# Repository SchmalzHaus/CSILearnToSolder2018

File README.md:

# LearnToSolder2018

## Introduction

In late 2018/early 2019 I taught a learn to solder class at the company I work for (CSI - www.csi360.com) because I thought it would be something enjoyable that I could teach my coworkers. Most of the class attendees had never soldered before. I designed a special circuit board for this class which mimics the functionality of one of the devices the company sells, but in miniature.

This site contains all of the information related to the class. If you want to learn more about how to solder, if you want to know what you need to purchase so you can solder at home, or if you want to make more of these boards for yourself or your organization, this site has everything you'll need.

If you want to reach Brian Schmalz (brian@schmalzaus.com) to ask any questions, please do so. 

All text files and designs on this site are Open Source. You are free to use these files and do whatever you wish with them.

## Design Details

The circuit board is designed in the shape of an OAD (Orbital Atherectomy Device). It has a speed switch, which wakes it up from sleep and allows you to select one of three speeds for the motor. The start/stop switch turns the motor on and off. The three green speed LEDs indicate which speed is currently selected. A small microcontroller has code which reads the switches and controls the LEDs and motor. A small FET is used to PWM the motor so various speeds can be achieved. The 3V lithium battery provides power to the circuit. The microcontroller stays asleep until the speed switch is pressed, and goes back to sleep (turning off the motor and LEDs) after 30 seconds of inactivity.

The code for the PIC microcontroller is included in this git repo, as well as the resulting HEX file. If you want to make this board on your own, you will need to program the microcontrollers with this HEX file. An ISCP connector footprint is provided under the battery holder so that the micro can be programed from the back by pressing in a 1x5 .1" header.

## CSI Learn T oSolder 2018 Kit Contents

* Qty 1 Bare Circuit Board (see above image for back and front views of the bare board) - note that the board used for the class already had the surface mount parts (3 of them) soldered on before the students got the boards.
* Qty 1 Speed Switch
* Qty 1 Start Switch
* Qty 3 Green LEDs
* Qty 1 Battery Holder
* Qty 1 Battery
* Qty 1 vibration motor
* Qty 1 black zip tie
* Qty 4 stick on rubber feet

## Tools

To solder electronic kits together, you will need (at a minimum)

### Soldering Iron

We do not recommend buying a soldering iron unless it is 'temperature controlled'. This means you get to set the tip temperature with a knob or buttons, and the iron will only heat up as much as it needs to in order to maintain that temperature. Using a non-temp controlled iron has, in our experience, led to lots of frustration and failed kits.

This is the iron we recommend, as we've had great experience with it and it is very inexpensive : [https://hobbyking.com/en_us/soldering-station-with-adjustable-heat-range-us-warehouse.html]

You can also by this same type of iron from many other places, including Amazon and E-bay, but the price tends to be a bit higher. Some of the companies listed below under Other Soldering Kits also sell tools like irons. There are also many other types of temperature controlled soldering irons which will work just as well.

### Solder

For beginners, we strongly recommend using leaded solder (rather than lead-free). The safety risk is very minimal (just be sure to wash your hands with soap when you are done) and it is far easier to get good soldered joints with leaded solder when you're just starting to learn soldering. You can buy leaded electronic solder at many on-line stores like SparkFun [https://www.sparkfun.com/products/9161] or Adafruit [https://www.adafruit.com/products/1886]. Make sure to buy 60/40 or 63/37 (those numbers represent the ratio of tin to lead in the solder) electronic solder - there are other solders out there (like silver solder for jewelry for example) that won't work for electronics.

### Brass Sponge

When you buy your iron, buy a bras sponge if the iron doesn't already come with it. These are much better than the watter sponge that comes with the iron for cleaning the tip of the soldering iron.

### Wire Cutter

All of the companies listed below sell small wire cutters, or you can get them locally at hardware stores too. The best kind is something that will allow you to cut off wires flush with the board - sometimes called 'flush cutters'. For example [https://www.sparkfun.com/products/11952] or [https://www.adafruit.com/products/152]

### Other tools

There are lots of other tools you can get to help you while solder. Third-hands can be very useful. Needle nose pliers, solder suckers, magnifying glasses, solder wick, wire strippers, etc.

## Kit Assembly Process (overview)

There are only a couple steps to assembling this kit, as it is very simple. If you have done soldering before, you can just walk through this overview of the steps to complete your kit. If you want to learn more about how to do the actual soldering of a joint, the following websites and resources will give you plenty of background materials and explanations:

https://learn.sparkfun.com/tutorials/how-to-solder---through-hole-soldering

http://www.howtogeek.com/63630/how-to-use-a-soldering-iron-a-beginners-guide/

https://cdn-learn.adafruit.com/downloads/pdf/adafruit-guide-excellent-soldering.pdf

### Steps:

1. Insert the two switches into the board. Make sure the switch pins go fully into the board from the top side to the back side. The switches snap down into the board - you sometimes have to press them in hard to get them to snap. Solder the four pins of each switch on the back side of the board.

2. Insert the battery holder to the front of the board, being careful to align the outline of the battery holder to the white outline on the top of the board (there is a square tab on the battery holder than needs to match up to the square tab part of the outline). While holding the battery holder into the board, flip it over and solder both battery holder pins.

3. Insert the three LEDs. Long wires go into square holes. You sometimes have to wiggle the LEDs a bit to get them to press all the way flat down on the top side of the board due to a thick spot on the LED leads. Bend the leads apart on the back side to keep the LEDs in place as you solder the LED wires on the back side of the board.

4. Add solder to the tops of the two motor pads so they form little mounds. Then reheat each mound in turn, inserting a motor wire while the solder is molten. Remove your iron and let the solder solidify without moving the motor wire. Do the same for the other motor wire.

5. Using the black zip tie, tie the motor to the board. There are two small holes in the board on either side of the motor. Put the zip tie through these holes, with the head of the zip tie on the top of the board. Cinch it down tight on the motor, but before you do so, make sure the black rubber sheath around the motor is pushed back away from the rotating weight. Clip the excess zip tie off.

6. Snap the start switch cap onto the start switch.

7. Insert the battery into the holder, flat shiny side up.

8. Put the four rubber sticky feet on the bottom of the board in the areas indicated with the white circles.

Now you can press the speed switch to wake up the OAD and select a speed (low, medium, high), then use the start switch to start and sto the motor. After 30 seconds of inactivity, the OAD will go back to sleep

## Other Soldering Kits

There are SO MANY kits available today, it's impossible to list all of them, or even the good ones. If you do a Google search for "electronic soldering kit" you will find lots of them out there. Some are easier than others, and some come with great instructions (and some don't).

We buy a lot of high quality soldering kits from the following on-line companies:

Evil Mad Scientist [http://shop.evilmadscientist.com/]
* Their Boldport Buggy is excellent [http://shop.evilmadscientist.com/]
* The Flickery Flame is a great beginner kit [http://shop.evilmadscientist.com/productsmenu/793]

Spark Fun Electronics [https://www.sparkfun.com/]
* They have a whole catagory of 'kits', some of which are soldering kits [https://www.sparkfun.com/categories/157]
* The SparkFun Simon Says - Through-Hole kit is really fun [https://www.sparkfun.com/products/10547]

Adafruit [https://www.adafruit.com/]
* The Drawdio is quite fun [https://www.adafruit.com/categories/28]
* Their Minty Boost is actually quite useful [https://www.adafruit.com/products/14]

SeeedStudio [http://www.seeedstudio.com/]
* Their 4-Soldering Zoo Kit looks super cute [https://www.seeedstudio.com/item_detail.html?p_id=1950]

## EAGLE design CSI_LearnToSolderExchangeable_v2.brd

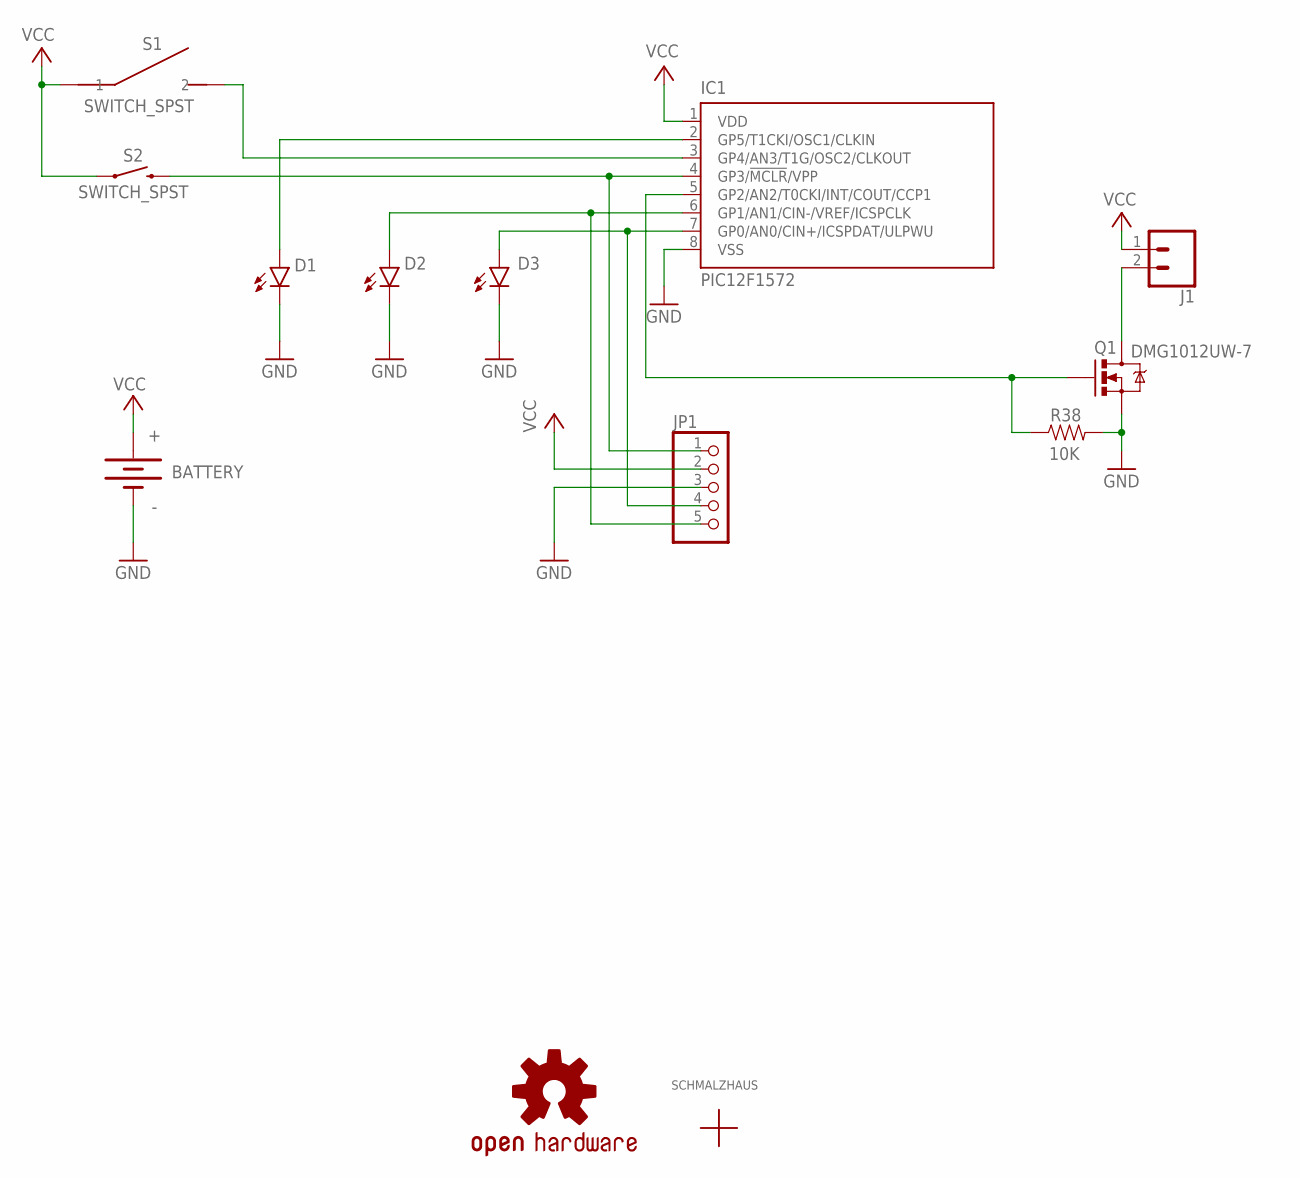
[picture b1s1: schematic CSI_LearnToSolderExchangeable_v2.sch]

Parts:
BATTERY: BATTERY20PTH; BATTCOM_20MM_PTH
D1, D2, D3: LED5MM
IC1: PIC12F1572; SO-08
J1: CONN_02LOCK_LONGPADS; 1X02_LOCK_LONGPADS
JP1: PINHD-1X5; 1X05
LOGO1: OSHW-LOGOMINI; OSHW-LOGO-MINI
Q1: DMG1012UW-7; SOT323
R38: 10K; 0603-RES
S1: SWITCH_SPST; OMRON-12MMX12MM_SPST-B3F-4000
S2: SWITCH_SPST; TACTILE_SWITCH_PTH_6.0MM
U$3: SCHMALZHAUSSCHMALZHAUS_SMALL; SCHMALZHAUS_SMALL

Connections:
B0_LEDCTL: IC1.5 (GP2/AN2/T0CKI/INT/COUT/CCP1), Q1.1 (G), R38.1
GND: BATTERY.2 (-), D1.K (C), D2.K (C), D3.K (C), IC1.8 (VSS), JP1.3, Q1.2 (S), R38.2
unnamed: IC1.4 (GP3/!MCLR!/VPP), JP1.1, S2.3 (2)
unnamed: IC1.3 (GP4/AN3/T1G/OSC2/CLKOUT), S1.3 (2), S1.4 (2)
unnamed: D3.A, IC1.7 (GP0/AN0/CIN+/ICSPDAT/ULPWU), JP1.4
unnamed: D2.A, IC1.6 (GP1/AN1/CIN-/VREF/ICSPCLK), JP1.5
unnamed: D1.A, IC1.2 (GP5/T1CKI/OSC1/CLKIN)
unnamed: J1.2, Q1.3 (D)
VCC: BATTERY.1 (+), IC1.1 (VDD), J1.1, JP1.2, S1.1, S1.2 (1), S2.1

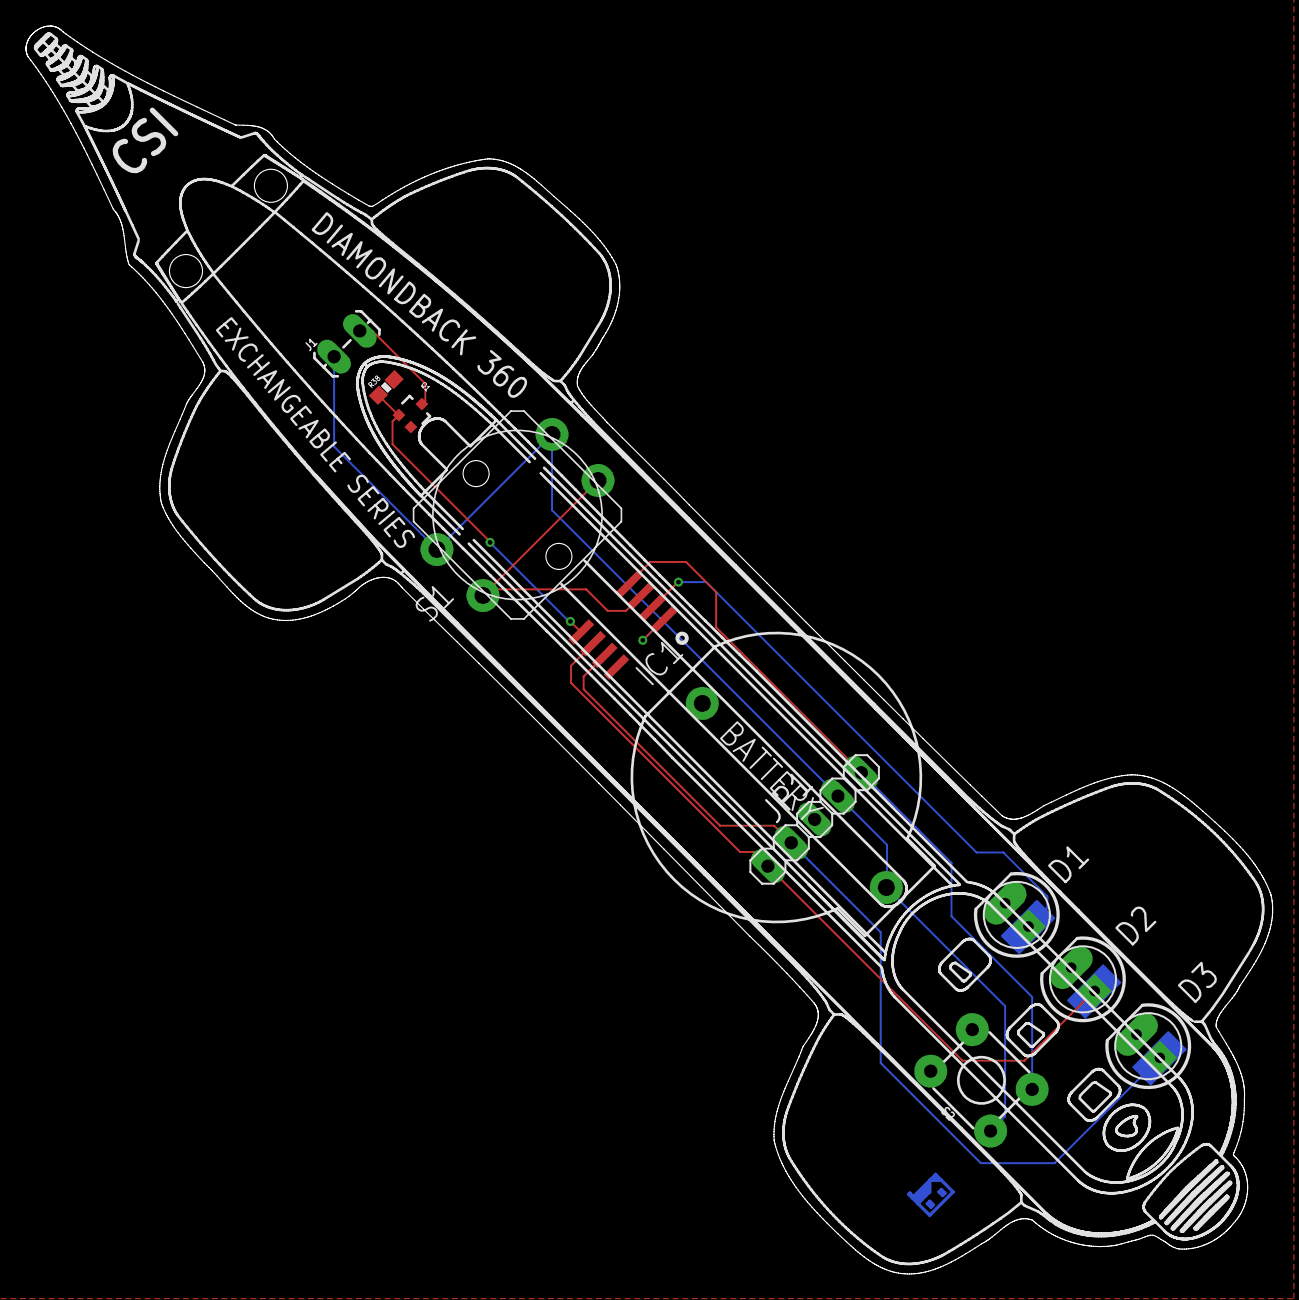
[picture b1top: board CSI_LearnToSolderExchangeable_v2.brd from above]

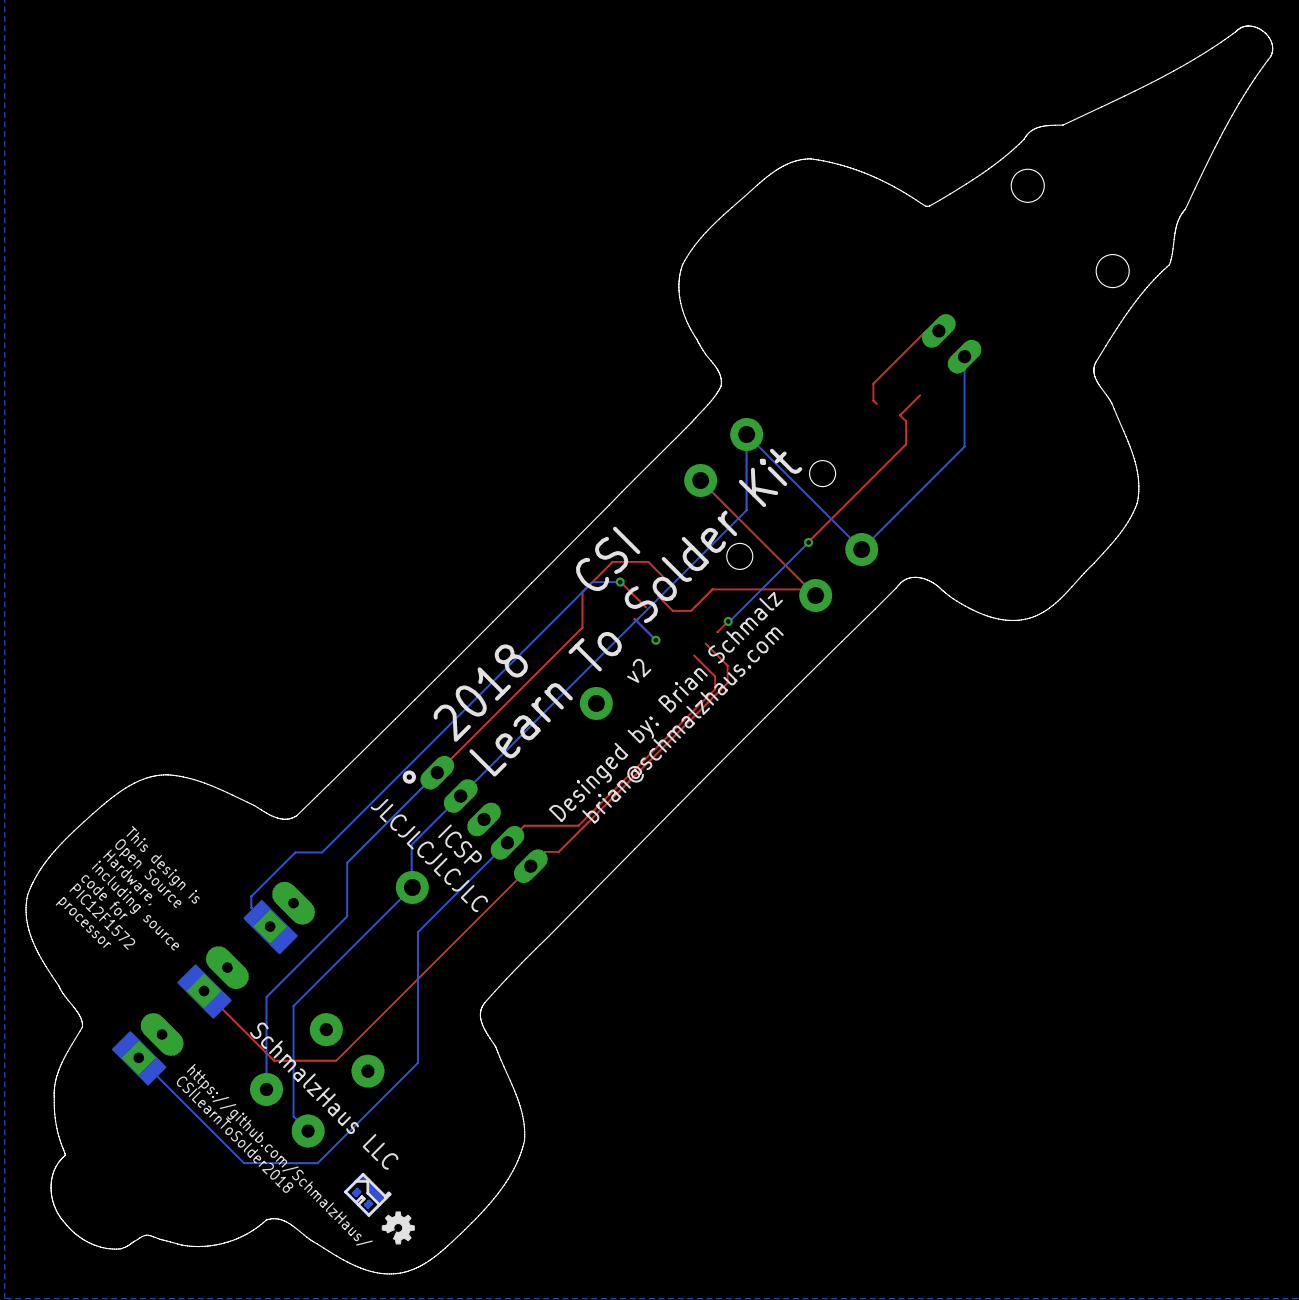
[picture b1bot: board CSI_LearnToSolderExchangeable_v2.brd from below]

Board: 2 copper layers, 95.8 x 95.9 mm, 13 parts (2 on the bottom side), 9 nets.

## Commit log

2018-10-17 Software working on v3 of board v3 of board checks out, working properly.
2018-10-25 Made new gerbers of v3.0 without the part names. Started the presentation.
2018-12-20 Updated readme.md
    Added CSI learn to solder specific information.
2018-12-20 Updated readme.md soldering iron link

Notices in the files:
parts and their libraries:
SparkFun-Aesthetics: Licensing: Creative Commons ShareAlike 4.0 International - https://creativecommons.org/licenses/by-sa/4.0
